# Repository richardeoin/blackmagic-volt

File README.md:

Blackmagic Volt

## Details

* The programming connector is an ARM 10-PIN Interface as described
  [here](http://www.keil.com/support/man/docs/ulink2/ulink2_hw_connectors.htm).

## Parts

* [Parts List](Parts.md)

## License

* [License](LICENSE.md)

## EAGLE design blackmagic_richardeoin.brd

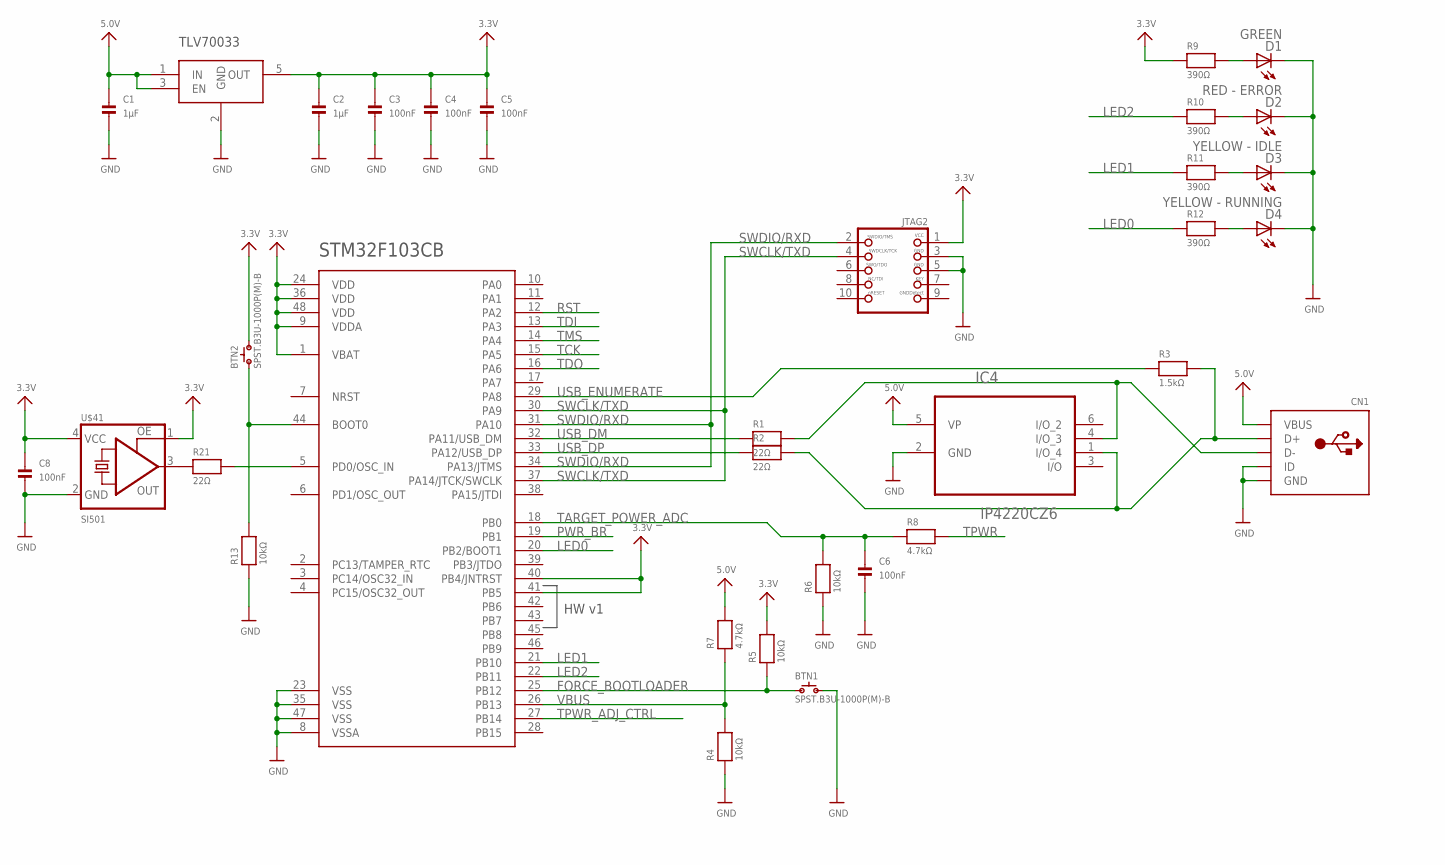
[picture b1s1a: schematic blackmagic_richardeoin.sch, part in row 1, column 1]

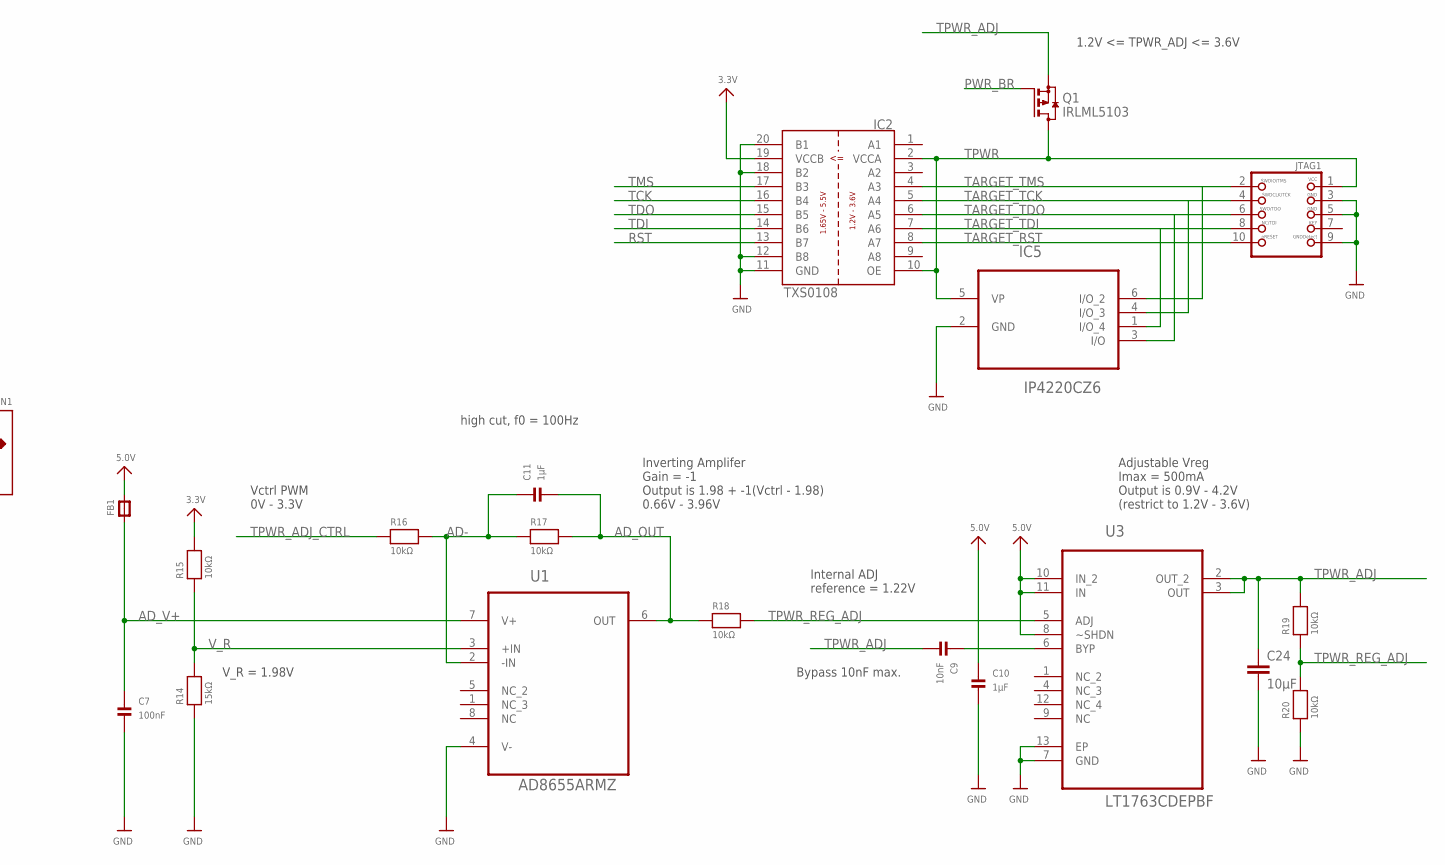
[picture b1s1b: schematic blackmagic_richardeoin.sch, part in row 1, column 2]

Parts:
BTN1, BTN2: SPST.B3U-1000P(M)-B; B3U-1000P(M)-B
C1, C2, C10, C11: 1µF; _0402
C3, C4, C5, C6, C7, C8: 100nF; _0402
C9: 10nF; _0402
C24: 10µF; C0603K
CN1: USBMINIB; USB-MINIB
D1: GREEN; CHIPLED_0603
D2: RED - ERROR; CHIPLED_0603
D3: YELLOW - IDLE; CHIPLED_0603
D4: YELLOW - RUNNING; CHIPLED_0603
FB1: FERRITE_0402; _0402
IC1: STM32F_48PIN; TQFP48
IC2: TXS0108; TSSOP20
IC3: TLV70033DCK; SC70-5L
IC4, IC5: IP4220CZ6; SOT95P275X110-6N
JTAG1, JTAG2: JTAG-CORTEXM3; 2X05_1.27MM_SMT
Q1: IRLML5103; SOT23
R1, R2, R21: 22Ω; _0402
R3: 1.5kΩ; _0402
R4, R5, R6, R13, R15, R16, R17, R18, R19, R20: 10kΩ; _0402
R7, R8: 4.7kΩ; _0402
R9, R10, R11, R12: 390Ω; _0402
R14: 15kΩ; _0402
U1: AD8655ARMZ; SOP65P490X110-8N
U3: LT1763CDEPBF; DFN400X300X80-13N
U$41: SI501; SI501_2X2.5

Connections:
3.3V: BTN2.2, C2.1, C3.1, C4.1, C5.1, IC1.1 (VBAT), IC1.9 (VDDA), IC1.24 (VDD), IC1.36 (VDD), IC1.40 (PB4/JNTRST), IC1.41 (PB5), IC1.48 (VDD), IC2.19 (VCCB), IC3.5 (OUT), JTAG2.1, R5.2, R9.1, R15.2, U$41.1 (OE)
5.0V: C1.1, C10.1, CN1.VBUS, FB1.2, IC3.1 (IN), IC3.3 (EN), IC4.5 (VP), R7.2, U3.8 (~SHDN), U3.10 (IN_2), U3.11 (IN)
AD-: C11.1, R16.2, R17.1, U1.2 (-IN)
AD_OUT: C11.2, R17.2, R18.1, U1.6 (OUT)
AD_V+: C7.1, FB1.1, U1.7 (V+)
BOOT0: BTN2.1, IC1.44 (BOOT0), R13.2
FORCE_BOOTLOADER: BTN1.1, IC1.25 (PB12), R5.1
GND: BTN1.2, C1.2, C2.2, C3.2, C4.2, C5.2, C6.2, C7.2, C8.2, C10.2, C24.2, CN1.GND, CN1.ID, D1.C, D2.C, D3.C, D4.C, IC1.8 (VSSA), IC1.23 (VSS), IC1.35 (VSS), IC1.47 (VSS), IC2.11 (GND), IC2.12 (B8), IC2.18 (B2), IC2.20 (B1), IC3.2 (GND), IC4.2 (GND), IC5.2 (GND), JTAG1.3, JTAG1.5, JTAG1.9, JTAG2.3, JTAG2.5, R4.1, R6.1, R13.1, R14.1, R20.1, U1.4 (V-), U3.7 (GND), U3.13 (EP), U$41.2 (GND)
IC8: C8.1, U$41.4 (VCC)
LED0: IC1.20 (PB2/BOOT1), R12.1
LED0_R: D4.A, R12.2
LED1: IC1.21 (PB10), R11.1
LED1_R: D3.A, R11.2
LED2: IC1.22 (PB11), R10.1
LED2_R: D2.A, R10.2
LED3_R: D1.A, R9.2
unnamed: IC1.5 (PD0/OSC_IN), R21.2
unnamed: R21.1, U$41.3 (OUT)
PWR_BR: IC1.19 (PB1), Q1.1 (G)
RST: IC1.12 (PA2), IC2.13 (B7)
SWCLK/TXD: IC1.30 (PA9), IC1.37 (PA14/JTCK/SWCLK), JTAG2.4
SWDIO/RXD: IC1.31 (PA10), IC1.34 (PA13/JTMS), JTAG2.2
TARGET_POWER_ADC: C6.1, IC1.18 (PB0), R6.2, R8.1
TARGET_RST: IC2.8 (A7), JTAG1.10
TARGET_TCK: IC2.5 (A4), IC5.4 (I/O_3), JTAG1.4
TARGET_TDI: IC2.7 (A6), IC5.1 (I/O_4), JTAG1.8
TARGET_TDO: IC2.6 (A5), IC5.3 (I/O), JTAG1.6
TARGET_TMS: IC2.4 (A3), IC5.6 (I/O_2), JTAG1.2
TCK: IC1.15 (PA5), IC2.16 (B4)
TDI: IC1.13 (PA3), IC2.14 (B6)
TDO: IC1.16 (PA6), IC2.15 (B5)
TMS: IC1.14 (PA4), IC2.17 (B3)
TPWR: IC2.2 (VCCA), IC2.10 (OE), IC5.5 (VP), JTAG1.1, Q1.3 (D), R8.2
TPWR_ADJ: C9.2, C24.1, Q1.2 (S), R19.2, U3.2 (OUT_2), U3.3 (OUT)
TPWR_ADJ_CTRL: IC1.27 (PB14), R16.1
TPWR_REG_ADJ: R18.2, R19.1, R20.2, U3.5 (ADJ)
TPWR_REG_BYP: C9.1, U3.6 (BYP)
USB_D+: CN1.D+, IC4.1 (I/O_4), R2.2, R3.2
USB_D-: CN1.D-, IC4.4 (I/O_3), R1.2
USB_DM: IC1.32 (PA11/USB_DM), R1.1
USB_DP: IC1.33 (PA12/USB_DP), R2.1
USB_ENUMERATE: IC1.29 (PA8), R3.1
VBUS: IC1.26 (PB13), R4.2, R7.1
V_R: R14.2, R15.1, U1.3 (+IN)

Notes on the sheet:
STM32F103CB
HW v1
TLV70033
1.2V <= TPWR_ADJ <= 3.6V
V_R = 1.98V
high cut, f0 = 100Hz
Internal ADJ reference = 1.22V
Bypass 10nF max.
Inverting Amplifer Gain = -1 Output is 1.98 + -1(Vctrl - 1.98) 0.66V - 3.96V
Vctrl PWM 0V - 3.3V
Adjustable Vreg Imax = 500mA Output is 0.9V - 4.2V (restrict to 1.2V - 3.6V)

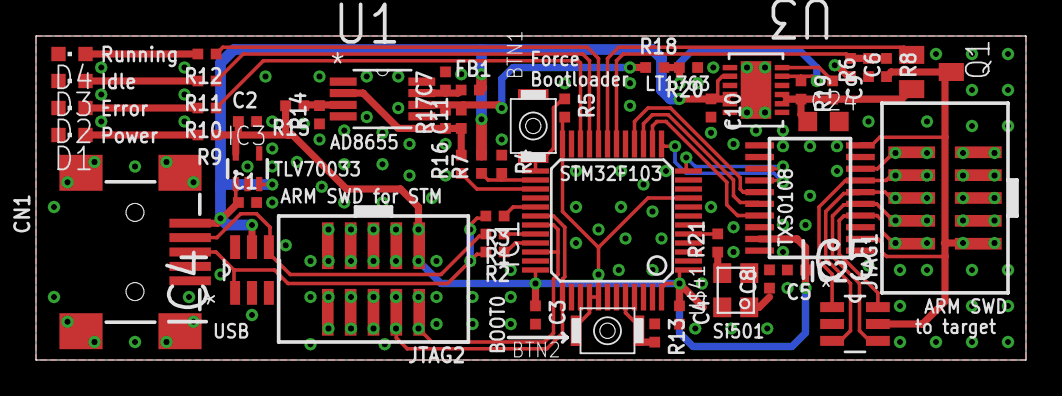
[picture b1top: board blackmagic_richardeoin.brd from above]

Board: 2 copper layers, 55.0 x 18.0 mm, 52 parts (0 on the bottom side), 44 nets.

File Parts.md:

# Parts List

| Part | Description | Supplier | Quantity Required | Notes
| ---  | ---         | ---       | ---               | ---
|STM32F103CBT6|STMICROELECTRONICS - MCU, 32BIT, CORTEX-M3, 72MHZ, LQFP-48|[1606327](http://uk.farnell.com/webapp/wcs/stores/servlet/Search?st=1606327)|1|IC1 mcu, cortex m3
|20021121-00010C4LF.|FCI - Board-To-Board Connector, Minitek127 20021121 Series, Surface Mount, Header, 10, 1.27 mm|[1865279](http://uk.farnell.com/webapp/wcs/stores/servlet/Search?st=1865279)|2|JTAG1, JTAG2 arm swd connector 1.27mm
|67503-1230|MOLEX - MINI USB, 2.0 OTG TYPE B, RCPT, SMT|[2313554](http://uk.farnell.com/webapp/wcs/stores/servlet/Search?st=2313554)|1|CN1 usb mini b
|B3U-1000P-B|OMRON ELECTRONIC COMPONENTS - SWITCH, SPST-NO, 0.05A, 12V, SMD, BOSS|[1333654](http://uk.farnell.com/webapp/wcs/stores/servlet/Search?st=1333654)|1|BTN1 spst tactile switch
|IRLML5103PBF|INTERNATIONAL RECTIFIER - MOSFET Transistor, P Channel, 610 mA, 30 V, 600 mohm, -10 V, -1 V|[8660085](http://uk.farnell.com/webapp/wcs/stores/servlet/Search?st=8660085)|1|Q1 p channel mosfet
|TXS0108EPWR|TEXAS INSTRUMENTS - TRANSLATOR, VOLTAGE, 8BIT, 20TSSOP|[1702548](http://uk.farnell.com/webapp/wcs/stores/servlet/Search?st=1702548)|1|IC2 voltage translator
|TLV70033DCKT|TEXAS INSTRUMENTS - IC, LDO, 200MA, 3.3V, 5SC70|[1815750](http://uk.farnell.com/webapp/wcs/stores/servlet/Search?st=1815750)|1|IC3 200mA 3.3v ldo
|IP4220CZ6,125|NXP - ESD Protection Device, 700 mV, SOT-457, 6|[1506629](http://uk.farnell.com/webapp/wcs/stores/servlet/Search?st=1506629)|2|IC4, IC5 usb esd protection, also swd esd protection
|AD8655ARMZ|ANALOG DEVICES - Operational Amplifier, Single, 28 MHz, 1, 11 V/Âµs, 2.7V to 5.5V, MSOP, 8|[2112576](http://uk.farnell.com/webapp/wcs/stores/servlet/Search?st=2112576)|1|IC6 rail-to-rail op amp AD8655
|LT1763IDE#PBF|LINEAR TECHNOLOGY - IC, LDO, ADJ, 0.5A, 12DFN|[1839216](http://uk.farnell.com/webapp/wcs/stores/servlet/Search?st=1839216)|1|IC7 LDO adj LT1763
|501ABA8M00000DAG|SILICON LABS - MEMS Oscillator, CMEMSÂ®, Si50x Series, 8 MHz, 30 ppm, 3.3 V, SMD, 2.5mm x 2mm, CMOS|[2394077](http://uk.farnell.com/webapp/wcs/stores/servlet/Search?st=2394077)|1|IC8 MEMS Osc. 8MHz

## Passives

| Part | Description | Supplier | Quantity Required | Notes
| ---  | ---         | ---       | ---               | ---

|MC0063W0603122R|MULTICOMP - Surface Mount Chip Resistor, Thick Film, MC Series, 22 ohm, 63 mW, Â± 1%, 50 V, 0603 [1608 Metric]|[9330844](http://uk.farnell.com/webapp/wcs/stores/servlet/Search?st=9330844)|2|R1, R2 22Ω
|MC0063W060311K5|MULTICOMP - Surface Mount Chip Resistor, Thick Film, MC Series, 1.5 kohm, 63 mW, Â± 1%, 50 V, 0603 [1608 Metric]|[9330607](http://uk.farnell.com/webapp/wcs/stores/servlet/Search?st=9330607)|1|R3 1.5kΩ
|MC0063W0603110K|MULTICOMP - Surface Mount Chip Resistor, Thick Film, MC Series, 10 kohm, 63 mW, Â± 1%, 50 V, 0603 [1608 Metric]|[9330399](http://uk.farnell.com/webapp/wcs/stores/servlet/Search?st=9330399)|4|R4, R5, R6, R13 10kΩ
|MC0063W060314K7|MULTICOMP - Surface Mount Chip Resistor, Thick Film, MC Series, 4.7 kohm, 63 mW, Â± 1%, 50 V, 0603 [1608 Metric]|[9331247](http://uk.farnell.com/webapp/wcs/stores/servlet/Search?st=9331247)|2|R7, R8 4.7kΩ
|MC0063W06031390R|MULTICOMP - Surface Mount Chip Resistor, Thick Film, MC Series, 390 ohm, 63 mW, Â± 1%, 50 V, 0603 [1608 Metric]|[9331131](http://uk.farnell.com/webapp/wcs/stores/servlet/Search?st=9331131)|4|R9, R10, R11, R12 390Ω
|KPT-1608SGC|KINGBRIGHT - LED, GREEN, 12MCD, 568NM, 0603|[2099223](http://uk.farnell.com/webapp/wcs/stores/servlet/Search?st=2099223)|1|D1 green led
|KPT-1608EC|KINGBRIGHT - LED, 0603, RED, 15MCD, 625NM|[2099221](http://uk.farnell.com/webapp/wcs/stores/servlet/Search?st=2099221)|1|D2 red led
|KPT-1608YC|KINGBRIGHT - LED, 0603, YELLOW, 8MCD, 588NM|[2099227](http://uk.farnell.com/webapp/wcs/stores/servlet/Search?st=2099227)|2|D3, D4 yellow led
|MC0603X105K100CT|MULTICOMP - SMD Multilayer Ceramic Capacitor, MC Series, 1 ÂµF, Â± 10%, X5R, 10 V, 0603 [1608 Metric]|[1759399](http://uk.farnell.com/webapp/wcs/stores/servlet/Search?st=1759399)|2|C1, C2 1µF
|MC0603B104K500CT|MULTICOMP - SMD Multilayer Ceramic Capacitor, MC Series, 0.1 ÂµF, Â± 10%, X7R, 50 V, 0603 [1608 Metric]|[1759122](http://uk.farnell.com/webapp/wcs/stores/servlet/Search?st=1759122)|4|C3, C4, C5, C6 100nF


## Useful items

| Part | Description | Supplier | Quantity Required | Notes
| ---  | ---         | ---       | ---               | ---
|FFSD-05-D-06.00-01-N|SAMTEC - RIBBON CABLE, IDC, 152.4MM, GREY, 10WAY|[1667659](http://uk.farnell.com/webapp/wcs/stores/servlet/Search?st=1667659)|0|10way 1.27mm

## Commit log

2015-10-12 Inital commit
2015-10-12 Fix license link
2015-10-12 Update parts list with 2x esd, split passives into separte list for clarity
2015-10-12 [Ooops] Fix partslist
2015-10-16 Update parts list for 0402 components, usb connx with pins

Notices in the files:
parts and their libraries:
microbuilder_v3: This work is placed in the public domain, and may be freely used for commercial and non-commercial work with the following conditions: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
SparkFun: Licensing: CC v3.0 Share-Alike You are welcome to use this library for commercial purposes.
